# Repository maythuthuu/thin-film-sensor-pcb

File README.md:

# Thin-Film Sensor PCB Module

## *VT CRO and The Workcell*

This PCB is the **first custom PCB I designed** for my robotics club, **VT CRO (Virginia Tech Competitive Robotics Organization)**, specifically for *[The Workcell](https://www.vtcro.org/design-teams/mwc)*.

The Workcell is a **fully autonomous 3D-printing farm** that VT CRO began developing in Fall 2023. The project went on to win national awards in Spring 2024, including the **Honda Innovation Award** and the **Additive Manufacturing Award** at the **National Robotics Challenge** in Ohio.

In Fall 2025, we decided to **open-source the project** and develop a **V2 model**, which includes major redesigns across **mechanical, software, and electrical**. As part of this effort, several **new custom PCBs** were designed for improved modularity, reliability, and scalability.

This repository focuses specifically on **one of those custom PCBs**. I won’t go into detail about the entire Workcell here, but feel free to explore VT CRO’s website for more background. Once the Workcell V2 is fully open-sourced, I’ll link the full project here as well.

---

## *Custom PCB Purpose*

This PCB is part of a **larger plate-detection system** used within the Workcell. The board is a **small, modular thin-film sensor PCB** designed to be soldered **at a 90-degree angle** to a larger **shift-register PCB** designed by one of my teammates.

Each thin-film sensor module is mounted along the **3D-printed plate shelves** in the Workcell. When a build plate is placed onto a shelf, the thin-film force sensor detects the applied pressure and generates an electrical signal. This signal is then routed to the shift-register PCB, which reports the **binary presence/absence state** of each plate to the main control software.

This modular approach allows the sensing system to scale easily while keeping each sensing node simple, compact, and replaceable.

---

## *Schematic and Parts*

Commercial thin-film sensor modules do exist (for example, [this module on Amazon](https://www.amazon.com/Fafeicy-3-3-5V-Pressure-Sensor-Compatible/dp/B097RR4KLC)), but a core part of **VT CRO’s culture** is building systems **custom and from scratch**. It’s more educational, more flexible, and honestly more fun. Plus, we get to fabricate the PCB in **black**, our signature color, and include our **eagle logo**.

The schematic itself is intentionally simple. The thin-film force sensor ([example sensor](https://www.amazon.com/dp/B0FGD267GK)) behaves as a **force-dependent variable resistor** and is used as part of a **voltage divider**, producing an output voltage that varies with applied pressure.

This analog voltage is interpreted by the downstream digital system as a **logic high or low**, depending on whether it crosses the input threshold of the shift-register IC. The resistor (R1) and capacitor (C1) form an **RC network** that was iteratively tuned to:
- Smooth sensor noise and contact bounce  
- Provide a reasonable response time  
- Meet the voltage threshold and timing requirements specified in the shift-register datasheet  

In KiCad, I used **solder pads** rather than connectors for the thin-film sensor to keep the footprint compact and mechanically robust when mounted at a right angle.

---

## *Images*

### Schematic

### PCB Editor

### 3D Render

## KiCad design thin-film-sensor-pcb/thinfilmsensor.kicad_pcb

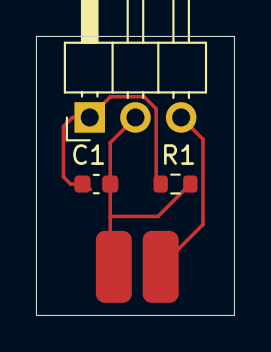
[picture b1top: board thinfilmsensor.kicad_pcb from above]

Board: 2 copper layers, 11.0 x 15.5 mm, 5 parts (0 on the bottom side), 3 nets.

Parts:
C1: 2.2nF; C_0603_1608Metric
J1: Conn_01x03_Pin; PinHeader_1x03_P2.54mm_Horizontal
J2, J3: Conn_01x01_Pin; SolderWirePad_1x01_SMD_2x4mm
R1: 18k; R_0603_1608Metric

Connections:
+5V: J1.3, J2.1
GND: C1.2, J1.1, R1.2
unnamed: C1.1, J1.2, J3.1, R1.1

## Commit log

2025-12-18 adding readme
2025-12-18 sensor files
2025-12-18 renaming file
2025-12-18 Adding readme info, and images
2025-12-18 UTF8 readme
2025-12-18 Fixing readme
